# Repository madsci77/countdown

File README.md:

This project is a multi-year Burning Man countdown.  When properly set, it will count
down the number of days until the man burns, and on the final day will switch to a
dancing animation.  The next day, the count resets and it begins counting down for
the next year.

Current draw is approximately 2 uA to 5 uA depending on the number of segments active.
Battery life on one CR2032 cell is about 5 years.

| Part | Description                | Price (qty 1) | Price (qty 10) |
|------|----------------------------|---------------|----------------|
| U1	 | Freescale MC9S08LL16CLH	| $2.95         |	$2.77          |
| LCD	 | Varionics VI-321-DP-RC-S	| $4.40	    | $3.28          |
| XTAL | CM51932768DZFT			| $1.20	    | $0.46          |
| BATT | Panasonic CR-2032L/F1N	| $1.10	    | $1.00          |
| C1-C6 | 0.1uF 0603 MLCC           |               |                |

Programming is via a TC2030 programming header with a non-standard pinout.  Sorry -
I only designed this for my own use and went with what I had available.

To set the starting time, you need to make sure that the interval[] array starts
with the current year's interval.  As provided, the code starts with 2013-2014.
You'll also need to set START_DAYS and START_MINS.

The code is fairly simple, but no great effort has been made to clean it up.
tod_ISD() runs once every minute and the current time is recorded in two places
in RAM.  If the MCU is rebooted (due to an SEU caused by a cosmic ray, for example)
counting will resume with the last recorded time if the backup copies are valid.

When the number of days remaining changes, the main loop updates the LCD pins
and shuts down until the next TOD interrupt.

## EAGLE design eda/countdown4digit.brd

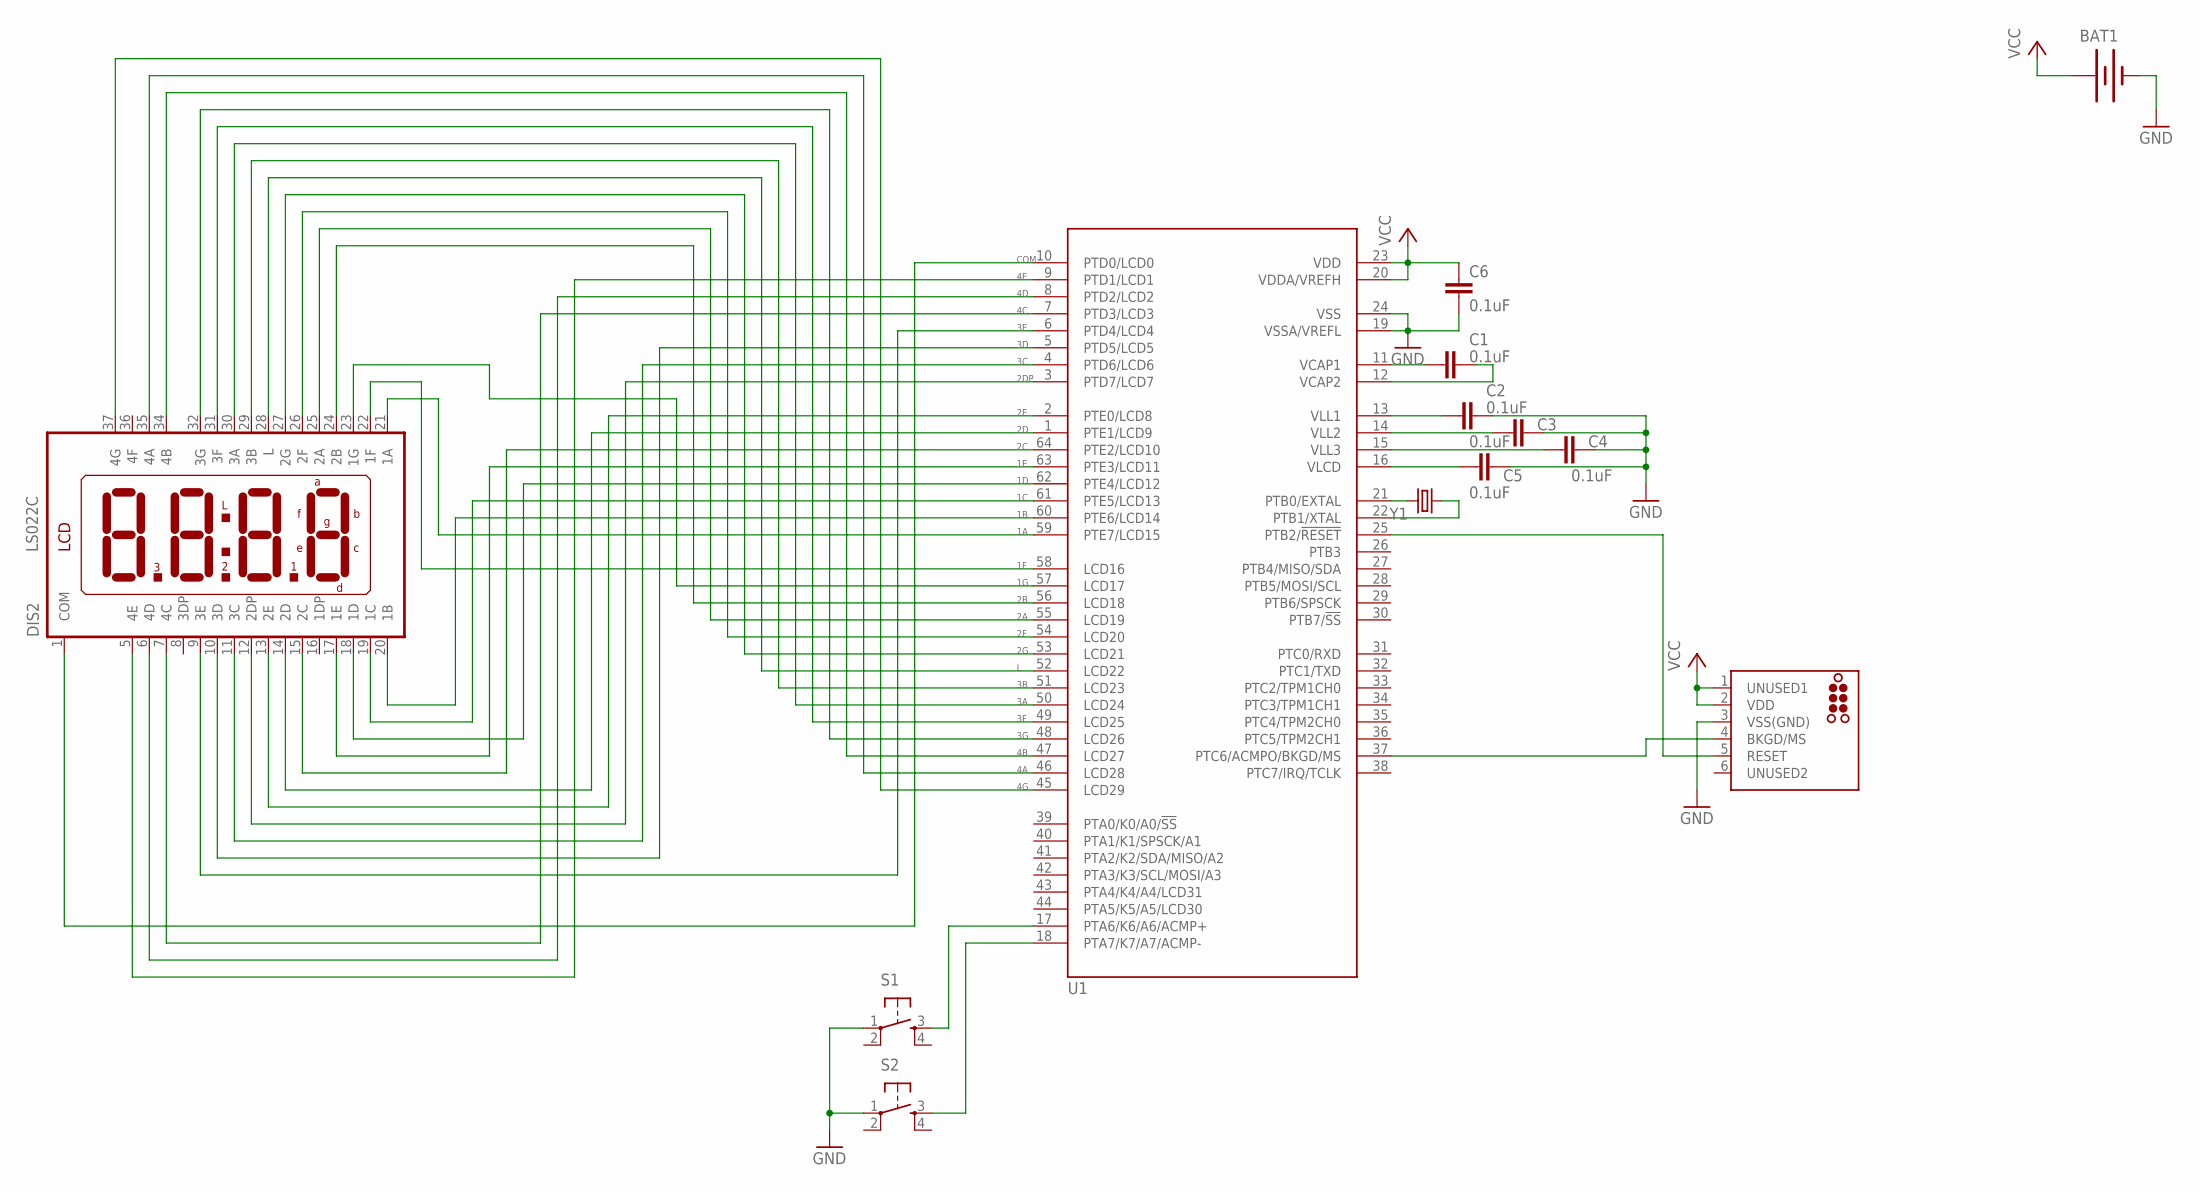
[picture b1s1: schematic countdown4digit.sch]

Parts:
BAT1: BATTERY12MM; BATTCON_12MM
BDM: TC2030-MCP-NL
C1, C2, C3, C4, C5, C6: 0.1uF; C0603K
DIS2: LS022C
S1, S2: TAC_SWITCHSMD; TACTILE_SWITCH_SMD
U1: MC9S08LL16; LQFP64
Y1: CRYSTALTC26H; TC26H

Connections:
1A: DIS2.21 (1A), U1.59 (PTE7/LCD15)
1B: DIS2.20 (1B), U1.60 (PTE6/LCD14)
1C: DIS2.19 (1C), U1.61 (PTE5/LCD13)
1D: DIS2.18 (1D), U1.62 (PTE4/LCD12)
1E: DIS2.17 (1E), U1.63 (PTE3/LCD11)
1F: DIS2.22 (1F), U1.58 (LCD16)
1G: DIS2.23 (1G), U1.57 (LCD17)
2A: DIS2.25 (2A), U1.55 (LCD19)
2B: DIS2.24 (2B), U1.56 (LCD18)
2C: DIS2.15 (2C), U1.64 (PTE2/LCD10)
2D: DIS2.14 (2D), U1.1 (PTE1/LCD9)
2DP: DIS2.12 (2DP), U1.3 (PTD7/LCD7)
2E: DIS2.13 (2E), U1.2 (PTE0/LCD8)
2F: DIS2.26 (2F), U1.54 (LCD20)
2G: DIS2.27 (2G), U1.53 (LCD21)
3A: DIS2.30 (3A), U1.50 (LCD24)
3B: DIS2.29 (3B), U1.51 (LCD23)
3C: DIS2.11 (3C), U1.4 (PTD6/LCD6)
3D: DIS2.10 (3D), U1.5 (PTD5/LCD5)
3E: DIS2.9 (3E), U1.6 (PTD4/LCD4)
3F: DIS2.31 (3F), U1.49 (LCD25)
3G: DIS2.32 (3G), U1.48 (LCD26)
4A: DIS2.35 (4A), U1.46 (LCD28)
4B: DIS2.34 (4B), U1.47 (LCD27)
4C: DIS2.7 (4C), U1.7 (PTD3/LCD3)
4D: DIS2.6 (4D), U1.8 (PTD2/LCD2)
4E: DIS2.5 (4E), U1.9 (PTD1/LCD1)
4G: DIS2.37 (4G), U1.45 (LCD29)
COM: DIS2.1 (COM), U1.10 (PTD0/LCD0)
GND: BAT1.GND (-), BDM.3 (VSS(GND)), C2.1, C3.1, C4.1, C5.1, C6.2, S1.1, S2.1, U1.19 (VSSA/VREFL), U1.24 (VSS)
L: DIS2.28 (L), U1.52 (LCD22)
unnamed: C1.2, U1.11 (VCAP1)
unnamed: C1.1, U1.12 (VCAP2)
unnamed: C2.2, U1.13 (VLL1)
unnamed: C3.2, U1.14 (VLL2)
unnamed: C4.2, U1.15 (VLL3)
unnamed: C5.2, U1.16 (VLCD)
unnamed: U1.21 (PTB0/EXTAL), Y1.2
unnamed: U1.22 (PTB1/XTAL), Y1.1
unnamed: BDM.4 (BKGD/MS), U1.37 (PTC6/ACMPO/BKGD/MS)
unnamed: BDM.5 (RESET), U1.25 (PTB2/!RESET)
unnamed: S1.3, U1.17 (PTA6/K6/A6/ACMP+)
unnamed: S2.3, U1.18 (PTA7/K7/A7/ACMP-)
VCC: BAT1.PWR@1 (+), BDM.1 (UNUSED1), BDM.2 (VDD), C6.1, U1.20 (VDDA/VREFH), U1.23 (VDD)

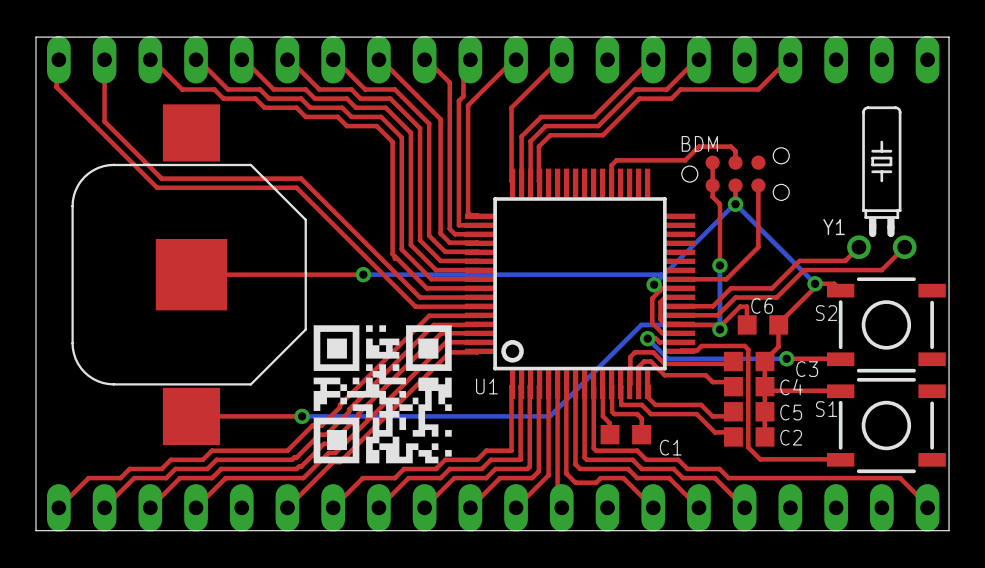
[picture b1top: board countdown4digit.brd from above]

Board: 2 copper layers, 50.7 x 27.4 mm, 14 parts (1 on the bottom side), 44 nets.

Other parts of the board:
U$1: QR-CODE-L-MED

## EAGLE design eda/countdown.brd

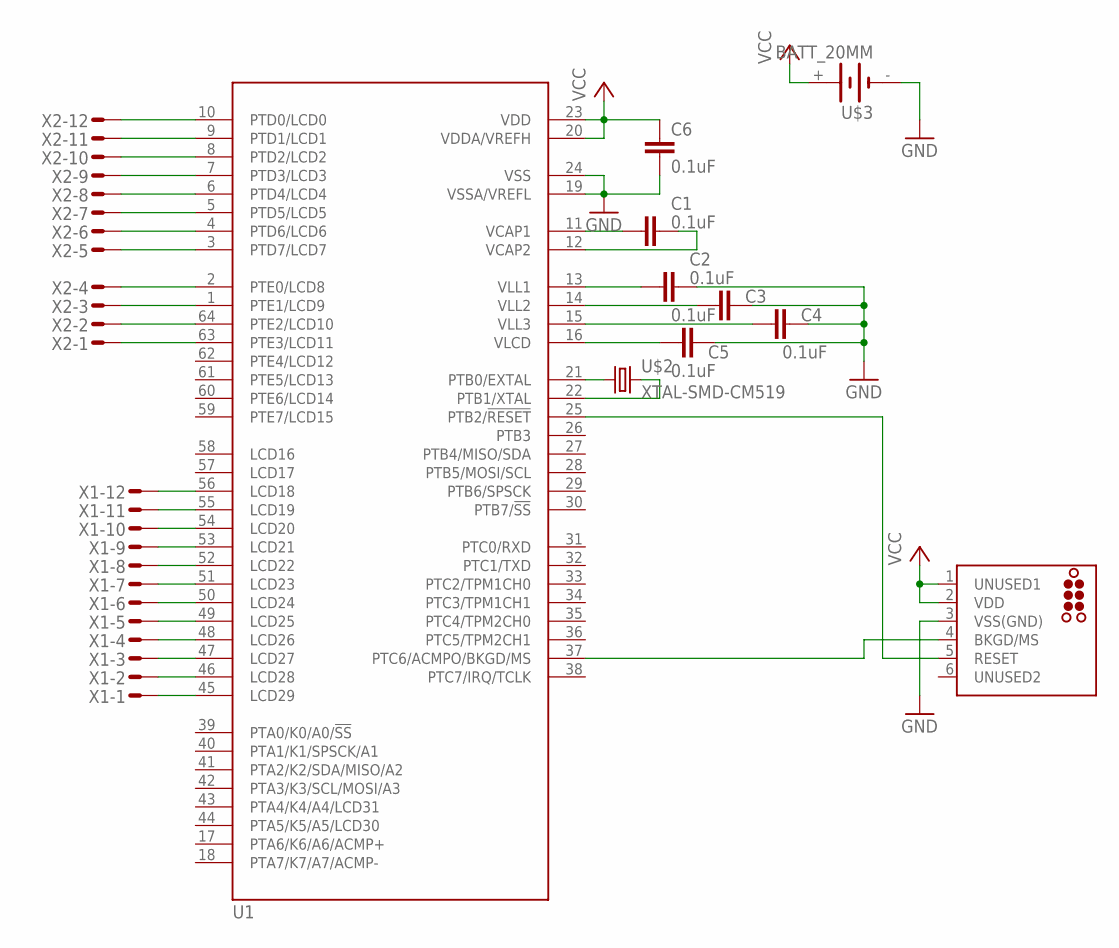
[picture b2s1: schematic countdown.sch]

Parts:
BDM: TC2030-MCP-NL
C1, C2, C3, C4, C5, C6: 0.1uF; C0603K
U1: MC9S08LL16; LQFP64
U$2: XTAL-SMD-CM519; SMD-XTAL-CM519
U$3: BATT_20MM
X1-, X2-: HEADER-12-EDGE

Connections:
GND: BDM.3 (VSS(GND)), C2.1, C3.1, C4.1, C5.1, C6.2, U1.19 (VSSA/VREFL), U1.24 (VSS), U$3.-
unnamed: U1.63 (PTE3/LCD11), X2-.1
unnamed: U1.64 (PTE2/LCD10), X2-.2
unnamed: U1.1 (PTE1/LCD9), X2-.3
unnamed: U1.2 (PTE0/LCD8), X2-.4
unnamed: U1.3 (PTD7/LCD7), X2-.5
unnamed: U1.4 (PTD6/LCD6), X2-.6
unnamed: U1.5 (PTD5/LCD5), X2-.7
unnamed: U1.6 (PTD4/LCD4), X2-.8
unnamed: U1.7 (PTD3/LCD3), X2-.9
unnamed: U1.8 (PTD2/LCD2), X2-.10
unnamed: U1.9 (PTD1/LCD1), X2-.11
unnamed: U1.10 (PTD0/LCD0), X2-.12
unnamed: U1.45 (LCD29), X1-.1
unnamed: U1.46 (LCD28), X1-.2
unnamed: U1.47 (LCD27), X1-.3
unnamed: U1.48 (LCD26), X1-.4
unnamed: U1.49 (LCD25), X1-.5
unnamed: U1.50 (LCD24), X1-.6
unnamed: U1.51 (LCD23), X1-.7
unnamed: U1.52 (LCD22), X1-.8
unnamed: U1.53 (LCD21), X1-.9
unnamed: U1.54 (LCD20), X1-.10
unnamed: U1.55 (LCD19), X1-.11
unnamed: U1.56 (LCD18), X1-.12
unnamed: C1.2, U1.11 (VCAP1)
unnamed: C1.1, U1.12 (VCAP2)
unnamed: C2.2, U1.13 (VLL1)
unnamed: C3.2, U1.14 (VLL2)
unnamed: C4.2, U1.15 (VLL3)
unnamed: C5.2, U1.16 (VLCD)
unnamed: U1.21 (PTB0/EXTAL), U$2.P$1 (1)
unnamed: U1.22 (PTB1/XTAL), U$2.P$2 (2)
unnamed: BDM.4 (BKGD/MS), U1.37 (PTC6/ACMPO/BKGD/MS)
unnamed: BDM.5 (RESET), U1.25 (PTB2/!RESET)
VCC: BDM.1 (UNUSED1), BDM.2 (VDD), C6.1, U1.20 (VDDA/VREFH), U1.23 (VDD), U$3.+

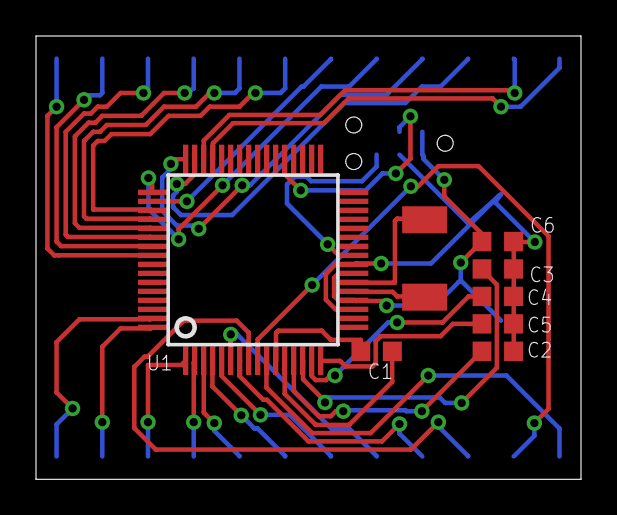
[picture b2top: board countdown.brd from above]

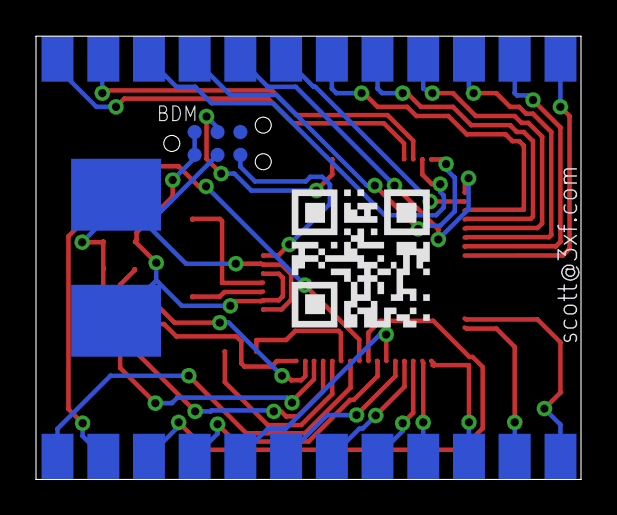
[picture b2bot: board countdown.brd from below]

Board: 2 copper layers, 30.3 x 24.6 mm, 13 parts (3 on the bottom side), 36 nets.

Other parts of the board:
U$1: QR-CODE-L-MED

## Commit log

2017-05-16 Created repository
2017-05-16 Updated description

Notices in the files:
parts and their libraries:
scott: ©2009 ROFA.cz
